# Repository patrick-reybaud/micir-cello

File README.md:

# MICIR — micro infrarouge pour violoncelle

Quatre couples émetteur infrarouge (SFH 4646) / phototransistor (SFH 3605), un par corde, sur un circuit collé au chevalet. La corde coupe le faisceau en vibrant ; le courant du phototransistor est le signal.

- `kicad/` : schéma et circuit (KiCad 5, projet `MICIR_cello3`), empreintes dans `MICIR_cello.pretty`, exports SVG des deux faces.
- `datasheet/` : fiche technique de l'émetteur.
- `essais-2020.wav` : premier essai sonore, octobre 2020.

Fiche du projet : https://electro-crea.com/projets/micir/

Publié pour qui voudrait reprendre ou adapter. Licence CERN-OHL-P v2 pour le matériel.

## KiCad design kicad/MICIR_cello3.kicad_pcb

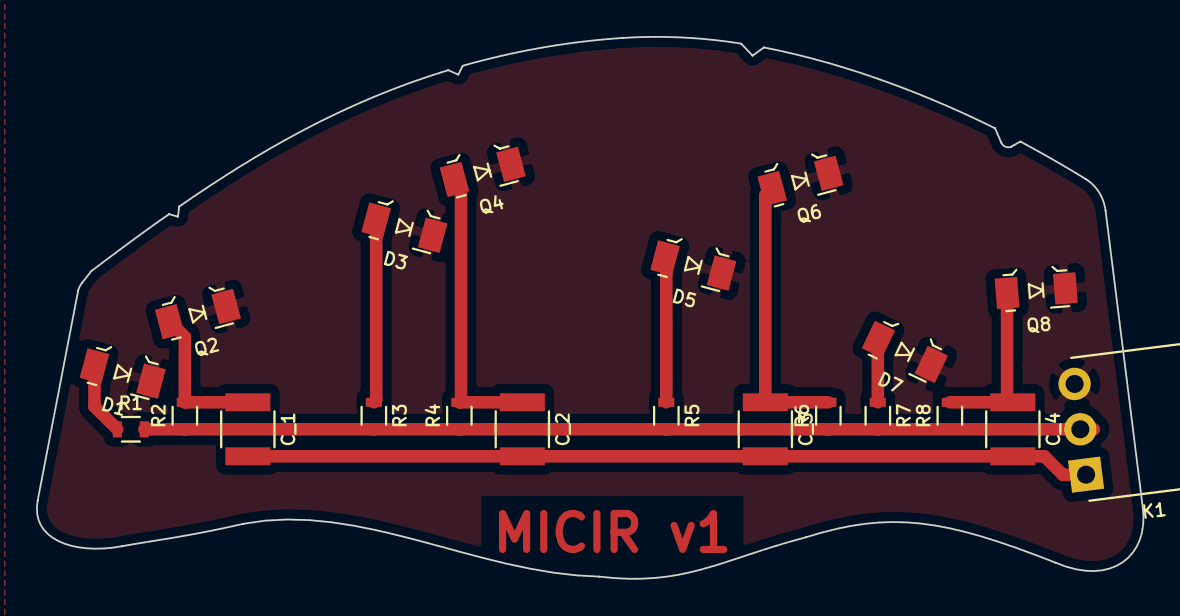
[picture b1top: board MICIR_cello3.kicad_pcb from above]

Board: 2 copper layers, 61.5 x 30.1 mm, 21 parts (0 on the bottom side), 11 nets.

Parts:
C_1, C_2, C_3, C_4: C_0040; C_1210
D1, D3, D5, D7: SFH4646
K1: K_0008; Pol_Pin_Header_1x3-P2.54-RA
Q2, Q4, Q6, Q8: SFH3605
R1, R3, R5, R7: 150; R_0603
R2, R4, R6, R8: R_0165; R_0603

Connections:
+5V: K1.2, R1.2, R2.1, R3.2, R4.1, R5.2, R6.1, R7.2, R8.1
GND: D1.1, D3.1, D5.1, D7.1, K1.3, Q2.2, Q4.2, Q6.2, Q8.2
unnamed: C_1.1, Q2.1, R2.2
unnamed: C_2.1, Q4.1, R4.2
unnamed: C_3.1, Q6.1, R6.2
unnamed: C_4.1, Q8.1, R8.2
unnamed: D1.2, R1.1
unnamed: D3.2, R3.1
unnamed: D5.2, R5.1
unnamed: D7.2, R7.1
OUT: C_1.2, C_2.2, C_3.2, C_4.2, K1.1
